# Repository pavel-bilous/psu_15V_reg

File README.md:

# Voltage regulator based on LM317 and LM337

## PCB rendered in 3d:

## Schematics:

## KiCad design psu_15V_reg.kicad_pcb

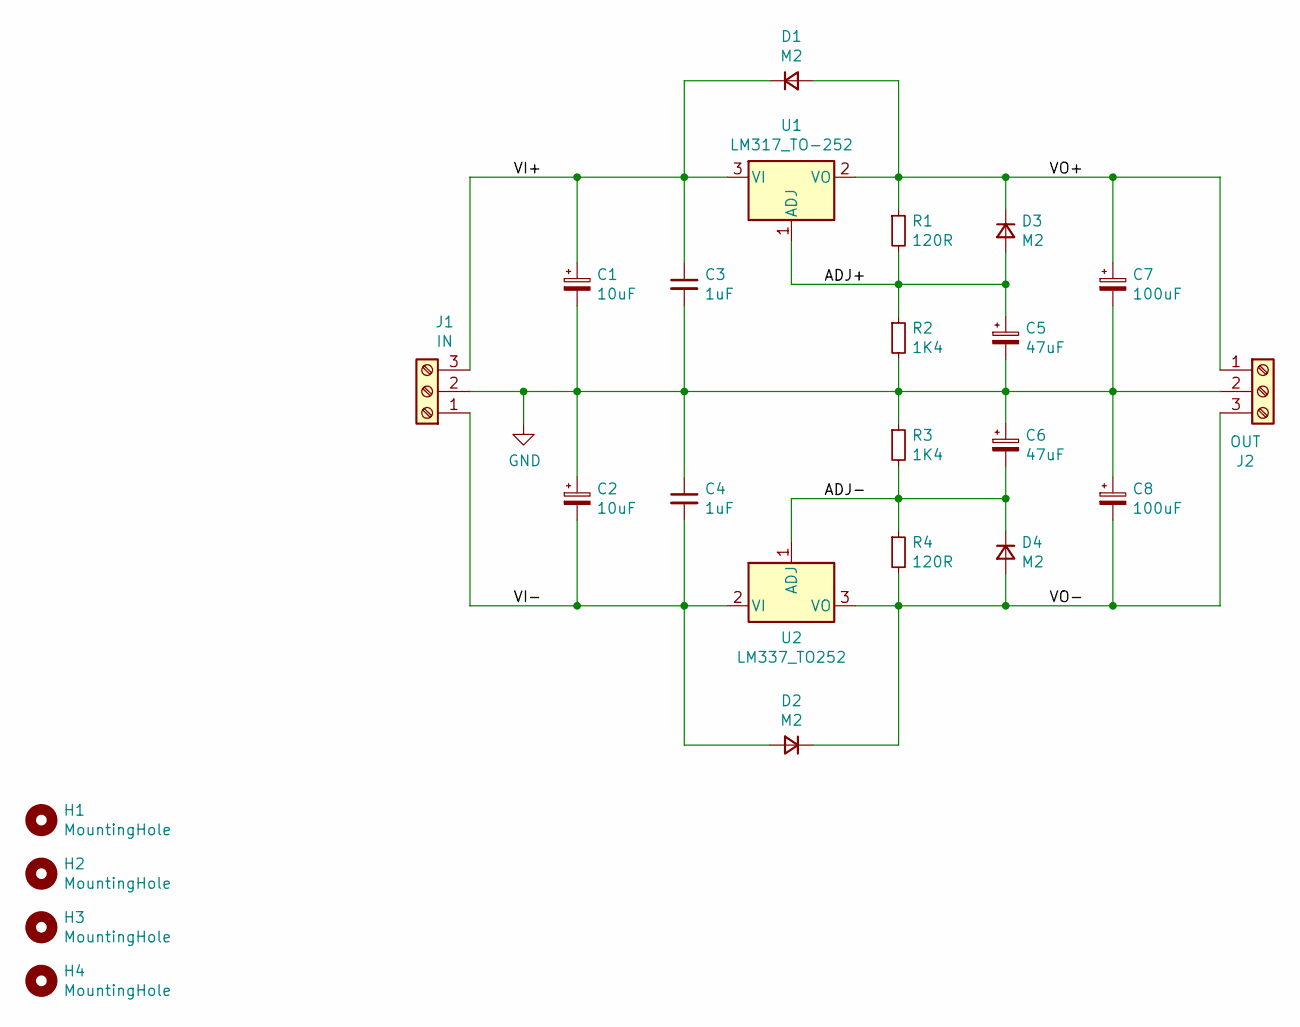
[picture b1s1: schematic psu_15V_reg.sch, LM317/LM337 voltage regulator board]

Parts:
C1, C2: 10uF; CP_Elec_5x5.3
C3, C4: 1uF; C_1206_3216Metric
C5, C6: 47uF; CP_Elec_6.3x5.9
C7, C8: 100uF; CP_Elec_8x6.9
D1, D2, D3, D4: M2; D_SMA
H1, H2, H3, H4: MountingHole; MountingHole_3.2mm_M3_Pad_Via
J1: IN; TerminalBlock_ Amphenol_01_03_P3.50mm
J2: OUT; TerminalBlock_ Amphenol_01_03_P3.50mm
R1, R4: 120R; R_1206_3216Metric
R2, R3: 1K4; R_1206_3216Metric
U1: LM317_TO-252; TO-252-2
U2: LM337_TO252; TO-252-2

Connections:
/ADJ+: C5.1, D3.2 (A), R1.2, R2.1, U1.1 (ADJ)
/ADJ-: C6.2, D4.1 (K), R3.2, R4.1, U2.1 (ADJ)
/VI+: C1.1, C3.1, D1.1 (K), J1.3, U1.3 (VI)
/VI-: C2.2, C4.2, D2.2 (A), J1.1, U2.2 (VI)
/VO+: C7.1, D1.2 (A), D3.1 (K), J2.1, R1.1, U1.2 (VO)
/VO-: C8.2, D2.1 (K), D4.2 (A), J2.3, R4.2, U2.3 (VO)
GND: C1.2, C2.1, C3.2, C4.1, C5.2, C6.1, C7.2, C8.1, J1.2, J2.2, R2.2, R3.1

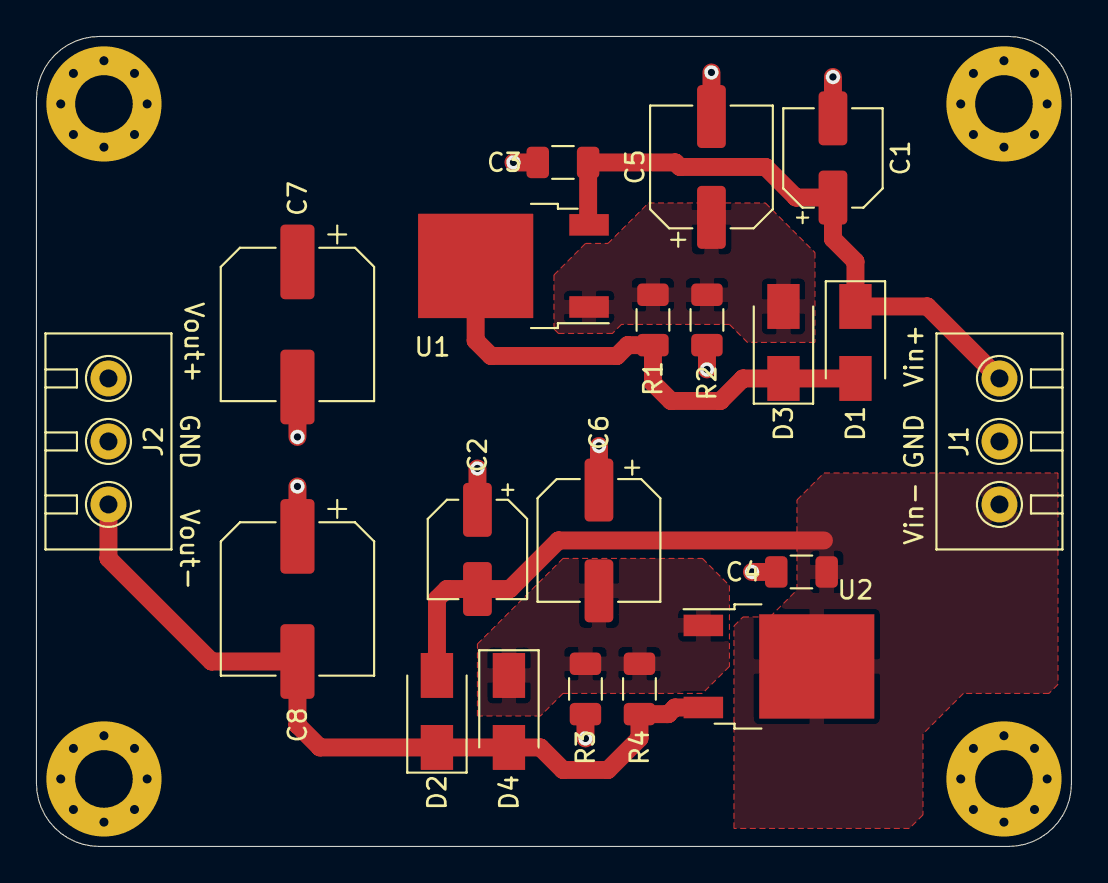
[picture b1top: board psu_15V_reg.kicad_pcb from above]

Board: 2 copper layers, 57.5 x 45.0 mm, 24 parts (0 on the bottom side), 7 nets.

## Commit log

2024-01-09 added sch
2024-01-10 progressing
2024-01-11 layout progress
2024-01-12 finished layout
2024-01-26 added bom
2024-02-02 rev2
